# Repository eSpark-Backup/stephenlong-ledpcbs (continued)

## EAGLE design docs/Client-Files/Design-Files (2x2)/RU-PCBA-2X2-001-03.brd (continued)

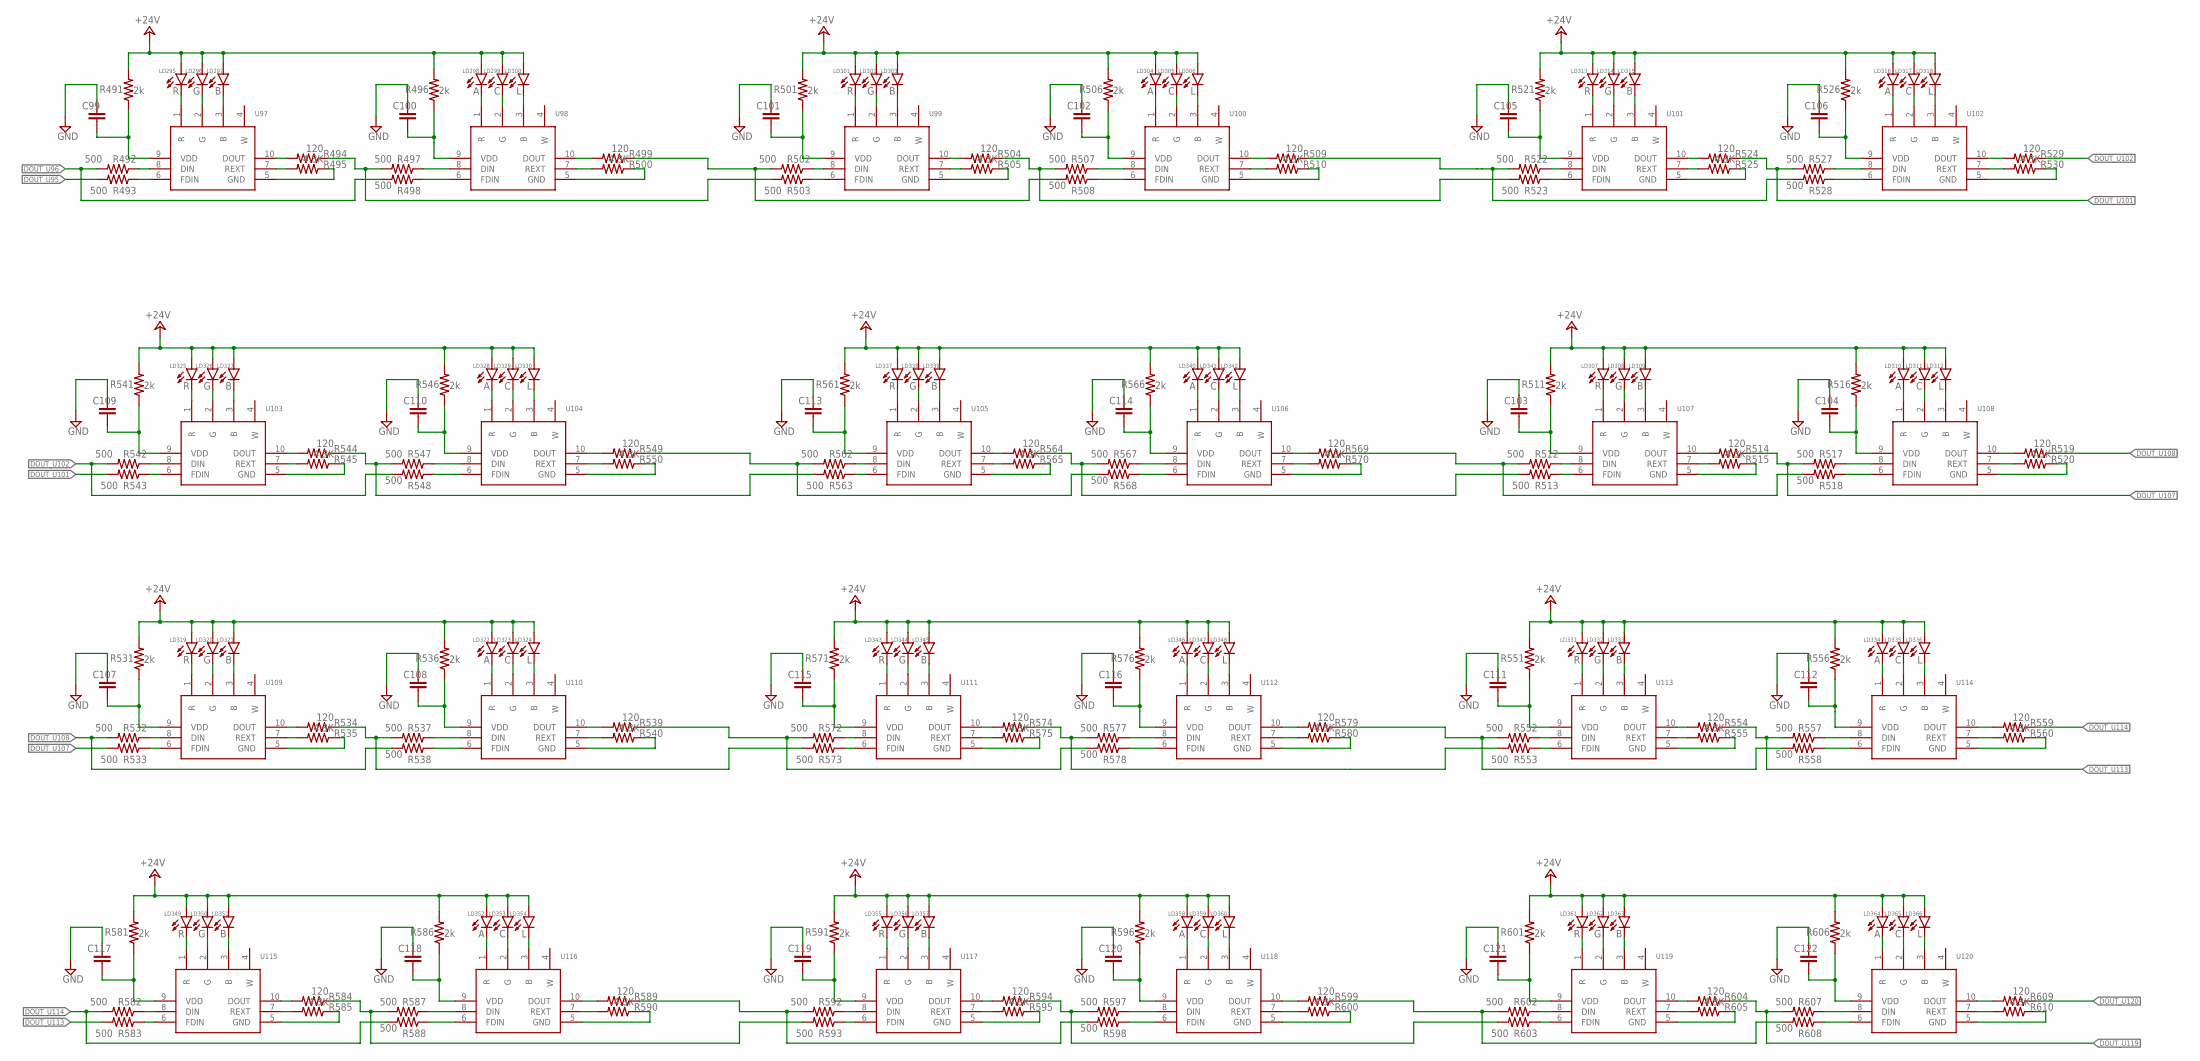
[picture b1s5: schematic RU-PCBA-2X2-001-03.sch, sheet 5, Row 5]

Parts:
C99, C100, C101, C102, C103, C104, C105, C106, C107, C108, C109, C110, C111, C112, C113, C114, C115, C116, C117, C118, C119, C120, C121, C122: C-EUC1206; C1206; MPN C_104
LD295, LD301, LD307, LD313, LD319, LD325, LD331, LD337, LD343, LD349, LD355, LD361: R; 5050LED; MPN R_5050
LD296, LD302, LD308, LD314, LD320, LD326, LD332, LD338, LD344, LD350, LD356, LD362: G; 5050LED; MPN G_5050
LD297, LD303, LD309, LD315, LD321, LD327, LD333, LD339, LD345, LD351, LD357, LD363: B; 5050LED; MPN B_5050
LD298, LD304, LD310, LD316, LD322, LD328, LD334, LD340, LD346, LD352, LD358, LD364: A; 5050LED; MPN A_5050
LD299, LD305, LD311, LD317, LD323, LD329, LD335, LD341, LD347, LD353, LD359, LD365: C; 5050LED; MPN C_5050
LD300, LD306, LD312, LD318, LD324, LD330, LD336, LD342, LD348, LD354, LD360, LD366: L; 5050LED; MPN L_5050
R491, R496, R501, R506, R511, R516, R521, R526, R531, R536, R541, R546, R551, R556, R561, R566, R571, R576, R581, R586, R591, R596, R601, R606: 2k; R1206; MPN R_VDD
R492, R493, R497, R498, R502, R503, R507, R508, R512, R513, R517, R518, R522, R523, R527, R528, R532, R533, R537, R538, R542, R543, R547, R548, R552, R553, R557, R558, R562, R563, R567, R568, R572, R573, R577, R578, R582, R583, R587, R588, R592, R593, R597, R598, R602, R603, R607, R608: 500; R0805; MPN R_500
R494, R499, R504, R509, R514, R519, R524, R529, R534, R539, R544, R549, R554, R559, R564, R569, R574, R579, R584, R589, R594, R599, R604, R609: 120; R0805; MPN R_120
R495, R500, R505, R510, R515, R520, R525, R530, R535, R540, R545, R550, R555, R560, R565, R570, R575, R580, R585, R590, R595, R600, R605, R610: 4.3K; R0805; MPN R_EXT
U97, U98, U99, U100, U101, U102, U103, U104, U105, U106, U107, U108, U109, U110, U111, U112, U113, U114, U115, U116, U117, U118, U119, U120: UCS7604; SOP100P600X175-10N; MPN UCS7604

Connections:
+24V: LD295.A, LD296.A, LD297.A, LD298.A, LD299.A, LD300.A, LD301.A, LD302.A, LD303.A, LD304.A, LD305.A, LD306.A, LD307.A, LD308.A, LD309.A, LD310.A, LD311.A, LD312.A, LD313.A, LD314.A, LD315.A, LD316.A, LD317.A, LD318.A, LD319.A, LD320.A, LD321.A, LD322.A, LD323.A, LD324.A, LD325.A, LD326.A, LD327.A, LD328.A, LD329.A, LD330.A, LD331.A, LD332.A, LD333.A, LD334.A, LD335.A, LD336.A, LD337.A, LD338.A, LD339.A, LD340.A, LD341.A, LD342.A, LD343.A, LD344.A, LD345.A, LD346.A, LD347.A, LD348.A, LD349.A, LD350.A, LD351.A, LD352.A, LD353.A, LD354.A, LD355.A, LD356.A, LD357.A, LD358.A, LD359.A, LD360.A, LD361.A, LD362.A, LD363.A, LD364.A, LD365.A, LD366.A, R491.2, R496.2, R501.2, R506.2, R511.2, R516.2, R521.2, R526.2, R531.2, R536.2, R541.2, R546.2, R551.2, R556.2, R561.2, R566.2, R571.2, R576.2, R581.2, R586.2, R591.2, R596.2, R601.2, R606.2; also elsewhere on the board
DOUT_U95: R493.2; also elsewhere on the board
DOUT_U96: R492.2, R498.2; also elsewhere on the board
DOUT_U101: R524.1, R527.2, R543.2
DOUT_U102: R529.1, R542.2, R548.2
DOUT_U107: R514.1, R517.2, R533.2
DOUT_U108: R519.1, R532.2, R538.2
DOUT_U113: R554.1, R557.2, R583.2
DOUT_U114: R559.1, R582.2, R588.2
DOUT_U119: R604.1, R607.2; also elsewhere on the board
DOUT_U120: R609.1; also elsewhere on the board
GND: C99.2, C100.2, C101.2, C102.2, C103.2, C104.2, C105.2, C106.2, C107.2, C108.2, C109.2, C110.2, C111.2, C112.2, C113.2, C114.2, C115.2, C116.2, C117.2, C118.2, C119.2, C120.2, C121.2, C122.2, R495.1, R500.1, R505.1, R510.1, R515.1, R520.1, R525.1, R530.1, R535.1, R540.1, R545.1, R550.1, R555.1, R560.1, R565.1, R570.1, R575.1, R580.1, R585.1, R590.1, R595.1, R600.1, R605.1, R610.1, U97.5 (GND), U98.5 (GND), U99.5 (GND), U100.5 (GND), U101.5 (GND), U102.5 (GND), U103.5 (GND), U104.5 (GND), U105.5 (GND), U106.5 (GND), U107.5 (GND), U108.5 (GND), U109.5 (GND), U110.5 (GND), U111.5 (GND), U112.5 (GND), U113.5 (GND), U114.5 (GND), U115.5 (GND), U116.5 (GND), U117.5 (GND), U118.5 (GND), U119.5 (GND), U120.5 (GND); also elsewhere on the board
unnamed: C99.1, R491.1, U97.9 (VDD)
unnamed: LD295.K (C), U97.1 (R)
unnamed: LD296.K (C), U97.2 (G)
unnamed: LD297.K (C), U97.3 (B)
unnamed: R492.1, U97.8 (DIN)
unnamed: R493.1, U97.6 (FDIN)
unnamed: R494.2, U97.10 (DOUT)
unnamed: R495.2, U97.7 (REXT)
unnamed: LD298.K (C), U98.1 (R)
unnamed: LD299.K (C), U98.2 (G)
unnamed: LD300.K (C), U98.3 (B)
unnamed: C100.1, R496.1, U98.9 (VDD)
unnamed: R497.1, U98.8 (DIN)
unnamed: R498.1, U98.6 (FDIN)
unnamed: R499.2, U98.10 (DOUT)
unnamed: R500.2, U98.7 (REXT)
unnamed: R499.1, R502.2, R508.2
unnamed: C101.1, R501.1, U99.9 (VDD)
unnamed: LD301.K (C), U99.1 (R)
unnamed: LD302.K (C), U99.2 (G)
unnamed: LD303.K (C), U99.3 (B)
unnamed: R502.1, U99.8 (DIN)
unnamed: R503.1, U99.6 (FDIN)
unnamed: R504.2, U99.10 (DOUT)
unnamed: R505.2, U99.7 (REXT)
unnamed: LD304.K (C), U100.1 (R)
unnamed: LD305.K (C), U100.2 (G)
unnamed: LD306.K (C), U100.3 (B)
unnamed: C102.1, R506.1, U100.9 (VDD)
unnamed: R507.1, U100.8 (DIN)
unnamed: R508.1, U100.6 (FDIN)
unnamed: R494.1, R497.2, R503.2
unnamed: R509.2, U100.10 (DOUT)
unnamed: R510.2, U100.7 (REXT)
unnamed: R509.1, R522.2, R528.2
unnamed: C103.1, R511.1, U107.9 (VDD)
unnamed: LD307.K (C), U107.1 (R)
unnamed: LD308.K (C), U107.2 (G)
unnamed: LD309.K (C), U107.3 (B)
unnamed: R512.1, U107.8 (DIN)
unnamed: R513.1, U107.6 (FDIN)
unnamed: R514.2, U107.10 (DOUT)
unnamed: R515.2, U107.7 (REXT)
unnamed: LD310.K (C), U108.1 (R)
unnamed: LD311.K (C), U108.2 (G)
unnamed: LD312.K (C), U108.3 (B)
unnamed: C104.1, R516.1, U108.9 (VDD)
unnamed: R517.1, U108.8 (DIN)
unnamed: R518.1, U108.6 (FDIN)
unnamed: R519.2, U108.10 (DOUT)
unnamed: R520.2, U108.7 (REXT)
unnamed: C105.1, R521.1, U101.9 (VDD)
unnamed: LD313.K (C), U101.1 (R)
unnamed: LD314.K (C), U101.2 (G)
unnamed: LD315.K (C), U101.3 (B)
unnamed: R522.1, U101.8 (DIN)
unnamed: R523.1, U101.6 (FDIN)
unnamed: R524.2, U101.10 (DOUT)
unnamed: R525.2, U101.7 (REXT)
unnamed: LD316.K (C), U102.1 (R)
unnamed: LD317.K (C), U102.2 (G)
unnamed: LD318.K (C), U102.3 (B)
unnamed: C106.1, R526.1, U102.9 (VDD)
unnamed: R527.1, U102.8 (DIN)
unnamed: R528.1, U102.6 (FDIN)
unnamed: R504.1, R507.2, R523.2
unnamed: R529.2, U102.10 (DOUT)
unnamed: R530.2, U102.7 (REXT)
unnamed: C107.1, R531.1, U109.9 (VDD)
unnamed: LD319.K (C), U109.1 (R)
unnamed: LD320.K (C), U109.2 (G)
unnamed: LD321.K (C), U109.3 (B)
unnamed: R532.1, U109.8 (DIN)
unnamed: R533.1, U109.6 (FDIN)
unnamed: R534.2, U109.10 (DOUT)
unnamed: R535.2, U109.7 (REXT)
unnamed: LD322.K (C), U110.1 (R)
unnamed: LD323.K (C), U110.2 (G)
unnamed: LD324.K (C), U110.3 (B)
unnamed: C108.1, R536.1, U110.9 (VDD)
unnamed: R537.1, U110.8 (DIN)
unnamed: R538.1, U110.6 (FDIN)
unnamed: R539.2, U110.10 (DOUT)
unnamed: R540.2, U110.7 (REXT)
unnamed: R539.1, R572.2, R578.2
unnamed: C109.1, R541.1, U103.9 (VDD)
unnamed: LD325.K (C), U103.1 (R)
unnamed: LD326.K (C), U103.2 (G)
unnamed: LD327.K (C), U103.3 (B)
unnamed: R542.1, U103.8 (DIN)
unnamed: R543.1, U103.6 (FDIN)
unnamed: R544.2, U103.10 (DOUT)
unnamed: R545.2, U103.7 (REXT)
unnamed: LD328.K (C), U104.1 (R)
unnamed: LD329.K (C), U104.2 (G)
unnamed: LD330.K (C), U104.3 (B)
unnamed: C110.1, R546.1, U104.9 (VDD)
unnamed: R547.1, U104.8 (DIN)
unnamed: R544.1, R547.2, R563.2
unnamed: R548.1, U104.6 (FDIN)
unnamed: R549.2, U104.10 (DOUT)
unnamed: R550.2, U104.7 (REXT)
unnamed: R549.1, R562.2, R568.2
unnamed: C111.1, R551.1, U113.9 (VDD)
unnamed: LD331.K (C), U113.1 (R)
unnamed: LD332.K (C), U113.2 (G)
unnamed: LD333.K (C), U113.3 (B)
unnamed: R552.1, U113.8 (DIN)
unnamed: R553.1, U113.6 (FDIN)
unnamed: R554.2, U113.10 (DOUT)
unnamed: R555.2, U113.7 (REXT)
unnamed: LD334.K (C), U114.1 (R)
unnamed: LD335.K (C), U114.2 (G)
unnamed: LD336.K (C), U114.3 (B)
unnamed: C112.1, R556.1, U114.9 (VDD)
unnamed: R557.1, U114.8 (DIN)
unnamed: R558.1, U114.6 (FDIN)
unnamed: R553.2, R574.1, R577.2
unnamed: R559.2, U114.10 (DOUT)
unnamed: R560.2, U114.7 (REXT)
unnamed: C113.1, R561.1, U105.9 (VDD)
unnamed: LD337.K (C), U105.1 (R)
unnamed: LD338.K (C), U105.2 (G)
unnamed: LD339.K (C), U105.3 (B)
unnamed: R562.1, U105.8 (DIN)
unnamed: R563.1, U105.6 (FDIN)
unnamed: R564.2, U105.10 (DOUT)
unnamed: R565.2, U105.7 (REXT)
unnamed: LD340.K (C), U106.1 (R)
unnamed: LD341.K (C), U106.2 (G)
unnamed: LD342.K (C), U106.3 (B)
unnamed: C114.1, R566.1, U106.9 (VDD)
unnamed: R567.1, U106.8 (DIN)
unnamed: R513.2, R564.1, R567.2
unnamed: R568.1, U106.6 (FDIN)
unnamed: R569.2, U106.10 (DOUT)
unnamed: R570.2, U106.7 (REXT)
unnamed: R512.2, R518.2, R569.1
unnamed: C115.1, R571.1, U111.9 (VDD)
unnamed: LD343.K (C), U111.1 (R)
unnamed: LD344.K (C), U111.2 (G)
unnamed: LD345.K (C), U111.3 (B)
unnamed: R572.1, U111.8 (DIN)
unnamed: R573.1, U111.6 (FDIN)
unnamed: R574.2, U111.10 (DOUT)
unnamed: R575.2, U111.7 (REXT)
unnamed: LD346.K (C), U112.1 (R)
unnamed: LD347.K (C), U112.2 (G)
unnamed: LD348.K (C), U112.3 (B)
unnamed: C116.1, R576.1, U112.9 (VDD)
unnamed: R577.1, U112.8 (DIN)
unnamed: R578.1, U112.6 (FDIN)
unnamed: R534.1, R537.2, R573.2
unnamed: R579.2, U112.10 (DOUT)
unnamed: R580.2, U112.7 (REXT)
unnamed: R552.2, R558.2, R579.1
unnamed: C117.1, R581.1, U115.9 (VDD)
unnamed: LD349.K (C), U115.1 (R)
unnamed: LD350.K (C), U115.2 (G)
unnamed: LD351.K (C), U115.3 (B)
unnamed: R582.1, U115.8 (DIN)
unnamed: R583.1, U115.6 (FDIN)
unnamed: R584.2, U115.10 (DOUT)
unnamed: R585.2, U115.7 (REXT)
unnamed: LD352.K (C), U116.1 (R)
unnamed: LD353.K (C), U116.2 (G)
unnamed: LD354.K (C), U116.3 (B)
unnamed: C118.1, R586.1, U116.9 (VDD)
unnamed: R587.1, U116.8 (DIN)
unnamed: R584.1, R587.2, R593.2
unnamed: R588.1, U116.6 (FDIN)
unnamed: R589.2, U116.10 (DOUT)
unnamed: R590.2, U116.7 (REXT)
unnamed: R589.1, R592.2, R598.2
unnamed: C119.1, R591.1, U117.9 (VDD)
unnamed: LD355.K (C), U117.1 (R)
unnamed: LD356.K (C), U117.2 (G)
unnamed: LD357.K (C), U117.3 (B)
unnamed: R592.1, U117.8 (DIN)
unnamed: R593.1, U117.6 (FDIN)
unnamed: R594.2, U117.10 (DOUT)
unnamed: R595.2, U117.7 (REXT)
unnamed: LD358.K (C), U118.1 (R)
unnamed: LD359.K (C), U118.2 (G)
unnamed: LD360.K (C), U118.3 (B)
unnamed: C120.1, R596.1, U118.9 (VDD)
unnamed: R597.1, U118.8 (DIN)
unnamed: R598.1, U118.6 (FDIN)
unnamed: R599.2, U118.10 (DOUT)
unnamed: R600.2, U118.7 (REXT)
unnamed: R599.1, R602.2, R608.2
unnamed: C121.1, R601.1, U119.9 (VDD)
unnamed: LD361.K (C), U119.1 (R)
unnamed: LD362.K (C), U119.2 (G)
unnamed: LD363.K (C), U119.3 (B)
unnamed: R602.1, U119.8 (DIN)
unnamed: R603.1, U119.6 (FDIN)
unnamed: R604.2, U119.10 (DOUT)
unnamed: R605.2, U119.7 (REXT)
unnamed: LD364.K (C), U120.1 (R)
unnamed: LD365.K (C), U120.2 (G)
unnamed: LD366.K (C), U120.3 (B)
unnamed: C122.1, R606.1, U120.9 (VDD)
unnamed: R607.1, U120.8 (DIN)
unnamed: R608.1, U120.6 (FDIN)
unnamed: R594.1, R597.2, R603.2
unnamed: R609.2, U120.10 (DOUT)
unnamed: R610.2, U120.7 (REXT)

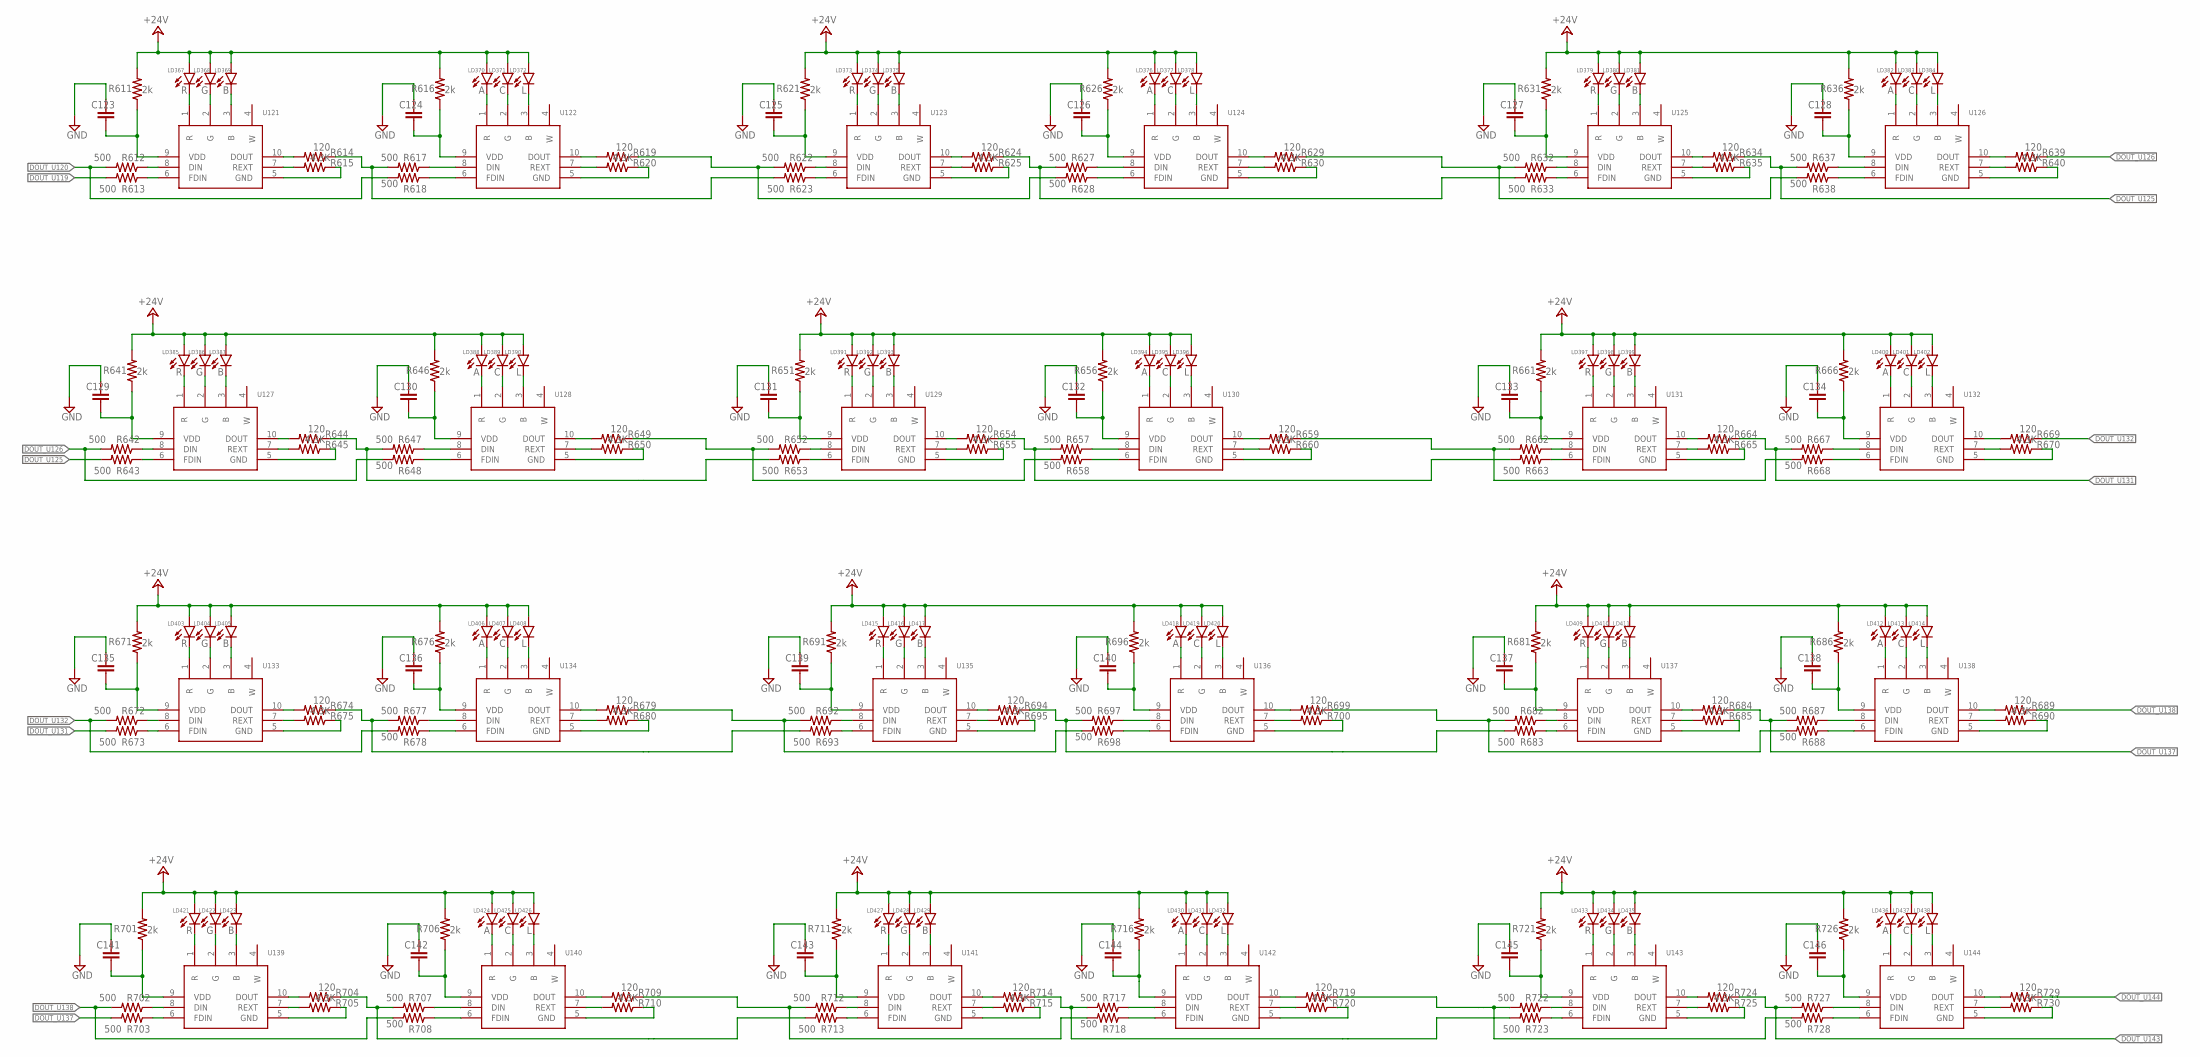
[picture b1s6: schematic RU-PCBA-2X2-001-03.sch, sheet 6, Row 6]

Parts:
C123, C124, C125, C126, C127, C128, C129, C130, C131, C132, C133, C134, C135, C136, C137, C138, C139, C140, C141, C142, C143, C144, C145, C146: C-EUC1206; C1206; MPN C_104
LD367, LD373, LD379, LD385, LD391, LD397, LD403, LD409, LD415, LD421, LD427, LD433: R; 5050LED; MPN R_5050
LD368, LD374, LD380, LD386, LD392, LD398, LD404, LD410, LD416, LD422, LD428, LD434: G; 5050LED; MPN G_5050
LD369, LD375, LD381, LD387, LD393, LD399, LD405, LD411, LD417, LD423, LD429, LD435: B; 5050LED; MPN B_5050
LD370, LD376, LD382, LD388, LD394, LD400, LD406, LD412, LD418, LD424, LD430, LD436: A; 5050LED; MPN A_5050
LD371, LD377, LD383, LD389, LD395, LD401, LD407, LD413, LD419, LD425, LD431, LD437: C; 5050LED; MPN C_5050
LD372, LD378, LD384, LD390, LD396, LD402, LD408, LD414, LD420, LD426, LD432, LD438: L; 5050LED; MPN L_5050
R611, R616, R621, R626, R631, R636, R641, R646, R651, R656, R661, R666, R671, R676, R681, R686, R691, R696, R701, R706, R711, R716, R721, R726: 2k; R1206; MPN R_VDD
R612, R613, R617, R618, R622, R623, R627, R628, R632, R633, R637, R638, R642, R643, R647, R648, R652, R653, R657, R658, R662, R663, R667, R668, R672, R673, R677, R678, R682, R683, R687, R688, R692, R693, R697, R698, R702, R703, R707, R708, R712, R713, R717, R718, R722, R723, R727, R728: 500; R0805; MPN R_500
R614, R619, R624, R629, R634, R639, R644, R649, R654, R659, R664, R669, R674, R679, R684, R689, R694, R699, R704, R709, R714, R719, R724, R729: 120; R0805; MPN R_120
R615, R620, R625, R630, R635, R640, R645, R650, R655, R660, R665, R670, R675, R680, R685, R690, R695, R700, R705, R710, R715, R720, R725, R730: 4.3K; R0805; MPN R_EXT
U121, U122, U123, U124, U125, U126, U127, U128, U129, U130, U131, U132, U133, U134, U135, U136, U137, U138, U139, U140, U141, U142, U143, U144: UCS7604; SOP100P600X175-10N; MPN UCS7604

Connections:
+24V: LD367.A, LD368.A, LD369.A, LD370.A, LD371.A, LD372.A, LD373.A, LD374.A, LD375.A, LD376.A, LD377.A, LD378.A, LD379.A, LD380.A, LD381.A, LD382.A, LD383.A, LD384.A, LD385.A, LD386.A, LD387.A, LD388.A, LD389.A, LD390.A, LD391.A, LD392.A, LD393.A, LD394.A, LD395.A, LD396.A, LD397.A, LD398.A, LD399.A, LD400.A, LD401.A, LD402.A, LD403.A, LD404.A, LD405.A, LD406.A, LD407.A, LD408.A, LD409.A, LD410.A, LD411.A, LD412.A, LD413.A, LD414.A, LD415.A, LD416.A, LD417.A, LD418.A, LD419.A, LD420.A, LD421.A, LD422.A, LD423.A, LD424.A, LD425.A, LD426.A, LD427.A, LD428.A, LD429.A, LD430.A, LD431.A, LD432.A, LD433.A, LD434.A, LD435.A, LD436.A, LD437.A, LD438.A, R611.2, R616.2, R621.2, R626.2, R631.2, R636.2, R641.2, R646.2, R651.2, R656.2, R661.2, R666.2, R671.2, R676.2, R681.2, R686.2, R691.2, R696.2, R701.2, R706.2, R711.2, R716.2, R721.2, R726.2; also elsewhere on the board
DOUT_U119: R613.2; also elsewhere on the board
DOUT_U120: R612.2, R618.2; also elsewhere on the board
DOUT_U125: R634.1, R637.2, R643.2
DOUT_U126: R639.1, R642.2, R648.2
DOUT_U131: R664.1, R667.2, R673.2
DOUT_U132: R669.1, R672.2, R678.2
DOUT_U137: R684.1, R687.2, R703.2
DOUT_U138: R689.1, R702.2, R708.2
DOUT_U143: R724.1, R727.2; also elsewhere on the board
DOUT_U144: R729.1; also elsewhere on the board
GND: C123.2, C124.2, C125.2, C126.2, C127.2, C128.2, C129.2, C130.2, C131.2, C132.2, C133.2, C134.2, C135.2, C136.2, C137.2, C138.2, C139.2, C140.2, C141.2, C142.2, C143.2, C144.2, C145.2, C146.2, R615.1, R620.1, R625.1, R630.1, R635.1, R640.1, R645.1, R650.1, R655.1, R660.1, R665.1, R670.1, R675.1, R680.1, R685.1, R690.1, R695.1, R700.1, R705.1, R710.1, R715.1, R720.1, R725.1, R730.1, U121.5 (GND), U122.5 (GND), U123.5 (GND), U124.5 (GND), U125.5 (GND), U126.5 (GND), U127.5 (GND), U128.5 (GND), U129.5 (GND), U130.5 (GND), U131.5 (GND), U132.5 (GND), U133.5 (GND), U134.5 (GND), U135.5 (GND), U136.5 (GND), U137.5 (GND), U138.5 (GND), U139.5 (GND), U140.5 (GND), U141.5 (GND), U142.5 (GND), U143.5 (GND), U144.5 (GND); also elsewhere on the board
unnamed: C123.1, R611.1, U121.9 (VDD)
unnamed: LD367.K (C), U121.1 (R)
unnamed: LD368.K (C), U121.2 (G)
unnamed: LD369.K (C), U121.3 (B)
unnamed: R612.1, U121.8 (DIN)
unnamed: R613.1, U121.6 (FDIN)
unnamed: R614.2, U121.10 (DOUT)
unnamed: R615.2, U121.7 (REXT)
unnamed: LD370.K (C), U122.1 (R)
unnamed: LD371.K (C), U122.2 (G)
unnamed: LD372.K (C), U122.3 (B)
unnamed: C124.1, R616.1, U122.9 (VDD)
unnamed: R617.1, U122.8 (DIN)
unnamed: R618.1, U122.6 (FDIN)
unnamed: R619.2, U122.10 (DOUT)
unnamed: R620.2, U122.7 (REXT)
unnamed: R619.1, R622.2, R628.2
unnamed: C125.1, R621.1, U123.9 (VDD)
unnamed: LD373.K (C), U123.1 (R)
unnamed: LD374.K (C), U123.2 (G)
unnamed: LD375.K (C), U123.3 (B)
unnamed: R622.1, U123.8 (DIN)
unnamed: R623.1, U123.6 (FDIN)
unnamed: R624.2, U123.10 (DOUT)
unnamed: R625.2, U123.7 (REXT)
unnamed: LD376.K (C), U124.1 (R)
unnamed: LD377.K (C), U124.2 (G)
unnamed: LD378.K (C), U124.3 (B)
unnamed: C126.1, R626.1, U124.9 (VDD)
unnamed: R627.1, U124.8 (DIN)
unnamed: R628.1, U124.6 (FDIN)
unnamed: R614.1, R617.2, R623.2
unnamed: R629.2, U124.10 (DOUT)
unnamed: R630.2, U124.7 (REXT)
unnamed: R629.1, R632.2, R638.2
unnamed: C127.1, R631.1, U125.9 (VDD)
unnamed: LD379.K (C), U125.1 (R)
unnamed: LD380.K (C), U125.2 (G)
unnamed: LD381.K (C), U125.3 (B)
unnamed: R632.1, U125.8 (DIN)
unnamed: R633.1, U125.6 (FDIN)
unnamed: R634.2, U125.10 (DOUT)
unnamed: R635.2, U125.7 (REXT)
unnamed: LD382.K (C), U126.1 (R)
unnamed: LD383.K (C), U126.2 (G)
unnamed: LD384.K (C), U126.3 (B)
unnamed: C128.1, R636.1, U126.9 (VDD)
unnamed: R637.1, U126.8 (DIN)
unnamed: R638.1, U126.6 (FDIN)
unnamed: R624.1, R627.2, R633.2
unnamed: R639.2, U126.10 (DOUT)
unnamed: R640.2, U126.7 (REXT)
unnamed: C129.1, R641.1, U127.9 (VDD)
unnamed: LD385.K (C), U127.1 (R)
unnamed: LD386.K (C), U127.2 (G)
unnamed: LD387.K (C), U127.3 (B)
unnamed: R642.1, U127.8 (DIN)
unnamed: R643.1, U127.6 (FDIN)
unnamed: R644.2, U127.10 (DOUT)
unnamed: R645.2, U127.7 (REXT)
unnamed: LD388.K (C), U128.1 (R)
unnamed: LD389.K (C), U128.2 (G)
unnamed: LD390.K (C), U128.3 (B)
unnamed: C130.1, R646.1, U128.9 (VDD)
unnamed: R647.1, U128.8 (DIN)
unnamed: R648.1, U128.6 (FDIN)
unnamed: R649.2, U128.10 (DOUT)
unnamed: R650.2, U128.7 (REXT)
unnamed: R649.1, R652.2, R658.2
unnamed: C131.1, R651.1, U129.9 (VDD)
unnamed: LD391.K (C), U129.1 (R)
unnamed: LD392.K (C), U129.2 (G)
unnamed: LD393.K (C), U129.3 (B)
unnamed: R652.1, U129.8 (DIN)
unnamed: R653.1, U129.6 (FDIN)
unnamed: R654.2, U129.10 (DOUT)
unnamed: R655.2, U129.7 (REXT)
unnamed: LD394.K (C), U130.1 (R)
unnamed: LD395.K (C), U130.2 (G)
unnamed: LD396.K (C), U130.3 (B)
unnamed: C132.1, R656.1, U130.9 (VDD)
unnamed: R657.1, U130.8 (DIN)
unnamed: R658.1, U130.6 (FDIN)
unnamed: R644.1, R647.2, R653.2
unnamed: R659.2, U130.10 (DOUT)
unnamed: R660.2, U130.7 (REXT)
unnamed: R659.1, R662.2, R668.2
unnamed: C133.1, R661.1, U131.9 (VDD)
unnamed: LD397.K (C), U131.1 (R)
unnamed: LD398.K (C), U131.2 (G)
unnamed: LD399.K (C), U131.3 (B)
unnamed: R662.1, U131.8 (DIN)
unnamed: R663.1, U131.6 (FDIN)
unnamed: R664.2, U131.10 (DOUT)
unnamed: R665.2, U131.7 (REXT)
unnamed: LD400.K (C), U132.1 (R)
unnamed: LD401.K (C), U132.2 (G)
unnamed: LD402.K (C), U132.3 (B)
unnamed: C134.1, R666.1, U132.9 (VDD)
unnamed: R667.1, U132.8 (DIN)
unnamed: R668.1, U132.6 (FDIN)
unnamed: R654.1, R657.2, R663.2
unnamed: R669.2, U132.10 (DOUT)
unnamed: R670.2, U132.7 (REXT)
unnamed: C135.1, R671.1, U133.9 (VDD)
unnamed: LD403.K (C), U133.1 (R)
unnamed: LD404.K (C), U133.2 (G)
unnamed: LD405.K (C), U133.3 (B)
unnamed: R672.1, U133.8 (DIN)
unnamed: R673.1, U133.6 (FDIN)
unnamed: R674.2, U133.10 (DOUT)
unnamed: R675.2, U133.7 (REXT)
unnamed: LD406.K (C), U134.1 (R)
unnamed: LD407.K (C), U134.2 (G)
unnamed: LD408.K (C), U134.3 (B)
unnamed: C136.1, R676.1, U134.9 (VDD)
unnamed: R677.1, U134.8 (DIN)
unnamed: R678.1, U134.6 (FDIN)
unnamed: R679.2, U134.10 (DOUT)
unnamed: R680.2, U134.7 (REXT)
unnamed: R679.1, R692.2, R698.2
unnamed: C137.1, R681.1, U137.9 (VDD)
unnamed: LD409.K (C), U137.1 (R)
unnamed: LD410.K (C), U137.2 (G)
unnamed: LD411.K (C), U137.3 (B)
unnamed: R682.1, U137.8 (DIN)
unnamed: R683.1, U137.6 (FDIN)
unnamed: R684.2, U137.10 (DOUT)
unnamed: R685.2, U137.7 (REXT)
unnamed: LD412.K (C), U138.1 (R)
unnamed: LD413.K (C), U138.2 (G)
unnamed: LD414.K (C), U138.3 (B)
unnamed: C138.1, R686.1, U138.9 (VDD)
unnamed: R687.1, U138.8 (DIN)
unnamed: R688.1, U138.6 (FDIN)
unnamed: R683.2, R694.1, R697.2
unnamed: R689.2, U138.10 (DOUT)
unnamed: R690.2, U138.7 (REXT)
unnamed: C139.1, R691.1, U135.9 (VDD)
unnamed: LD415.K (C), U135.1 (R)
unnamed: LD416.K (C), U135.2 (G)
unnamed: LD417.K (C), U135.3 (B)
unnamed: R692.1, U135.8 (DIN)
unnamed: R693.1, U135.6 (FDIN)
unnamed: R694.2, U135.10 (DOUT)
unnamed: R695.2, U135.7 (REXT)
unnamed: LD418.K (C), U136.1 (R)
unnamed: LD419.K (C), U136.2 (G)
unnamed: LD420.K (C), U136.3 (B)
unnamed: C140.1, R696.1, U136.9 (VDD)
unnamed: R697.1, U136.8 (DIN)
unnamed: R698.1, U136.6 (FDIN)
unnamed: R674.1, R677.2, R693.2
unnamed: R699.2, U136.10 (DOUT)
unnamed: R700.2, U136.7 (REXT)
unnamed: R682.2, R688.2, R699.1
unnamed: C141.1, R701.1, U139.9 (VDD)
unnamed: LD421.K (C), U139.1 (R)
unnamed: LD422.K (C), U139.2 (G)
unnamed: LD423.K (C), U139.3 (B)
unnamed: R702.1, U139.8 (DIN)
unnamed: R703.1, U139.6 (FDIN)
unnamed: R704.2, U139.10 (DOUT)
unnamed: R705.2, U139.7 (REXT)
unnamed: LD424.K (C), U140.1 (R)
unnamed: LD425.K (C), U140.2 (G)
unnamed: LD426.K (C), U140.3 (B)
unnamed: C142.1, R706.1, U140.9 (VDD)
unnamed: R707.1, U140.8 (DIN)
unnamed: R708.1, U140.6 (FDIN)
unnamed: R709.2, U140.10 (DOUT)
unnamed: R710.2, U140.7 (REXT)
unnamed: R709.1, R712.2, R718.2
unnamed: C143.1, R711.1, U141.9 (VDD)
unnamed: LD427.K (C), U141.1 (R)
unnamed: LD428.K (C), U141.2 (G)
unnamed: LD429.K (C), U141.3 (B)
unnamed: R712.1, U141.8 (DIN)
unnamed: R713.1, U141.6 (FDIN)
unnamed: R714.2, U141.10 (DOUT)
unnamed: R715.2, U141.7 (REXT)
unnamed: LD430.K (C), U142.1 (R)
unnamed: LD431.K (C), U142.2 (G)
unnamed: LD432.K (C), U142.3 (B)
unnamed: C144.1, R716.1, U142.9 (VDD)
unnamed: R717.1, U142.8 (DIN)
unnamed: R718.1, U142.6 (FDIN)
unnamed: R704.1, R707.2, R713.2
unnamed: R719.2, U142.10 (DOUT)
unnamed: R720.2, U142.7 (REXT)
unnamed: R719.1, R722.2, R728.2
unnamed: C145.1, R721.1, U143.9 (VDD)
unnamed: LD433.K (C), U143.1 (R)
unnamed: LD434.K (C), U143.2 (G)
unnamed: LD435.K (C), U143.3 (B)
unnamed: R722.1, U143.8 (DIN)
unnamed: R723.1, U143.6 (FDIN)
unnamed: R724.2, U143.10 (DOUT)
unnamed: R725.2, U143.7 (REXT)
unnamed: LD436.K (C), U144.1 (R)
unnamed: LD437.K (C), U144.2 (G)
unnamed: LD438.K (C), U144.3 (B)
unnamed: C146.1, R726.1, U144.9 (VDD)
unnamed: R727.1, U144.8 (DIN)
unnamed: R728.1, U144.6 (FDIN)
unnamed: R714.1, R717.2, R723.2
unnamed: R729.2, U144.10 (DOUT)
unnamed: R730.2, U144.7 (REXT)
